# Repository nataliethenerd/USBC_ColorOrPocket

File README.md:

# USBC_ColorOrPocket
USB C for the Game Boy Color or Pocket... or Pocket Color

## NOTES
- This board is for LiPo mods. The anchor points connect to the Game Boy's GND, the pad goes to 5V.
- BOM is a 6 pin USB C and two 0402 5.1K resistors (these are to allow charging via a USB C to C cable)
- USB.zip are the gerbers, download them, order them from your fave PCB fab
- CHECK THE LICENCE PLS

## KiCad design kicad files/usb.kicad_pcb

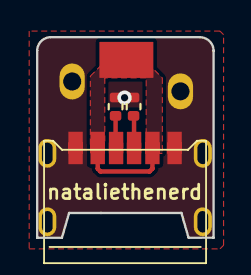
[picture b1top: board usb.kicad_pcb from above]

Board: 2 copper layers, 9.8 x 11.1 mm, 3 parts (0 on the bottom side), 4 nets.

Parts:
J1: USB_C_Receptacle_USB2.0; TYPE-C-31-M-17
R1, R2: 5.1K; R_0402_1005Metric

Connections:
+5V: J1.A9 (VBUS), J1.B9 (VBUS)
GND: J1.1, J1.A12 (GND), J1.B12 (GND), R1.1, R2.2
unnamed: J1.A5 (CC1), R1.2
unnamed: J1.B5 (CC2), R2.1

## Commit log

2024-03-05 Rename CC-BY-4.0 to licence
